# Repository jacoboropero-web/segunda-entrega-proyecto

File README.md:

# Estación de Monitoreo Ambiental con Ventilación Automática (ESP32)

Proyecto del curso Diseño Electrónico CAD, Universidad Autónoma de Manizales.
Autores: Jacobo Ropero y Santiago Rueda. Docente: Iván Alberto Arias.

## Contenido

| Carpeta | Contenido |
|---|---|
| `reporte/` | Reporte de Avance 2 (formato IEEE, PDF) |
| `hardware/estacion_kicad/` | Proyecto KiCad 7: esquemático jerárquico (3 hojas), PCB de 4 capas de 80 × 60 mm y librería de símbolos propia |
| `hardware/estacion_kicad/fab/` | Archivos de fabricación: Gerber y taladrado, BOM y CPL para JLCPCB, esquemático en PDF |
| `firmware/` | Firmware preliminar para ESP32-WROOM-32E (PlatformIO/Arduino), con 15 pruebas unitarias de la lógica de control. Ver `firmware/README.md` |
| `imagenes/` | Capturas de KiCad: editor de esquemas, ERC, editor de placas, pistas, ratsnest y vistas 3D |

## Abrir el proyecto

Abrir `hardware/estacion_kicad/estacion.kicad_pro` con KiCad 7 o posterior.

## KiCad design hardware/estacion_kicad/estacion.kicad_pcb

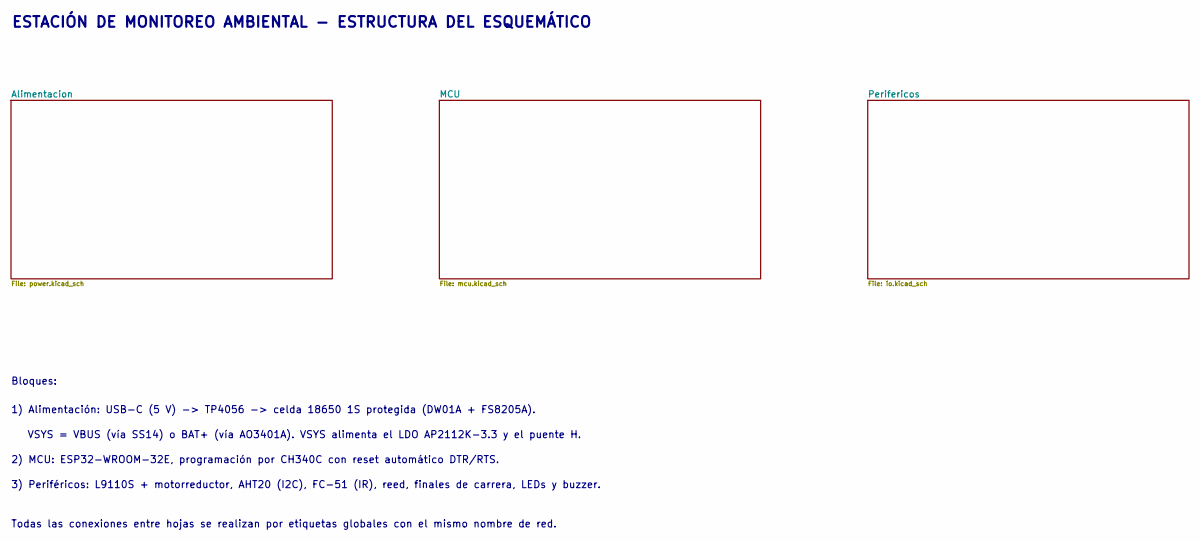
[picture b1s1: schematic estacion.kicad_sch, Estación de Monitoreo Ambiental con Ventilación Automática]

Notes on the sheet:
ESTACIÓN DE MONITOREO AMBIENTAL - ESTRUCTURA DEL ESQUEMÁTICO
Bloques:
1) Alimentación: USB-C (5 V) -> TP4056 -> celda 18650 1S protegida (DW01A + FS8205A).
VSYS = VBUS (vía SS14) o BAT+ (vía AO3401A). VSYS alimenta el LDO AP2112K-3.3 y el puente H.
2) MCU: ESP32-WROOM-32E, programación por CH340C con reset automático DTR/RTS.
3) Periféricos: L9110S + motorreductor, AHT20 (I2C), FC-51 (IR), reed, finales de carrera, LEDs y buzzer.
Todas las conexiones entre hojas se realizan por etiquetas globales con el mismo nombre de red.

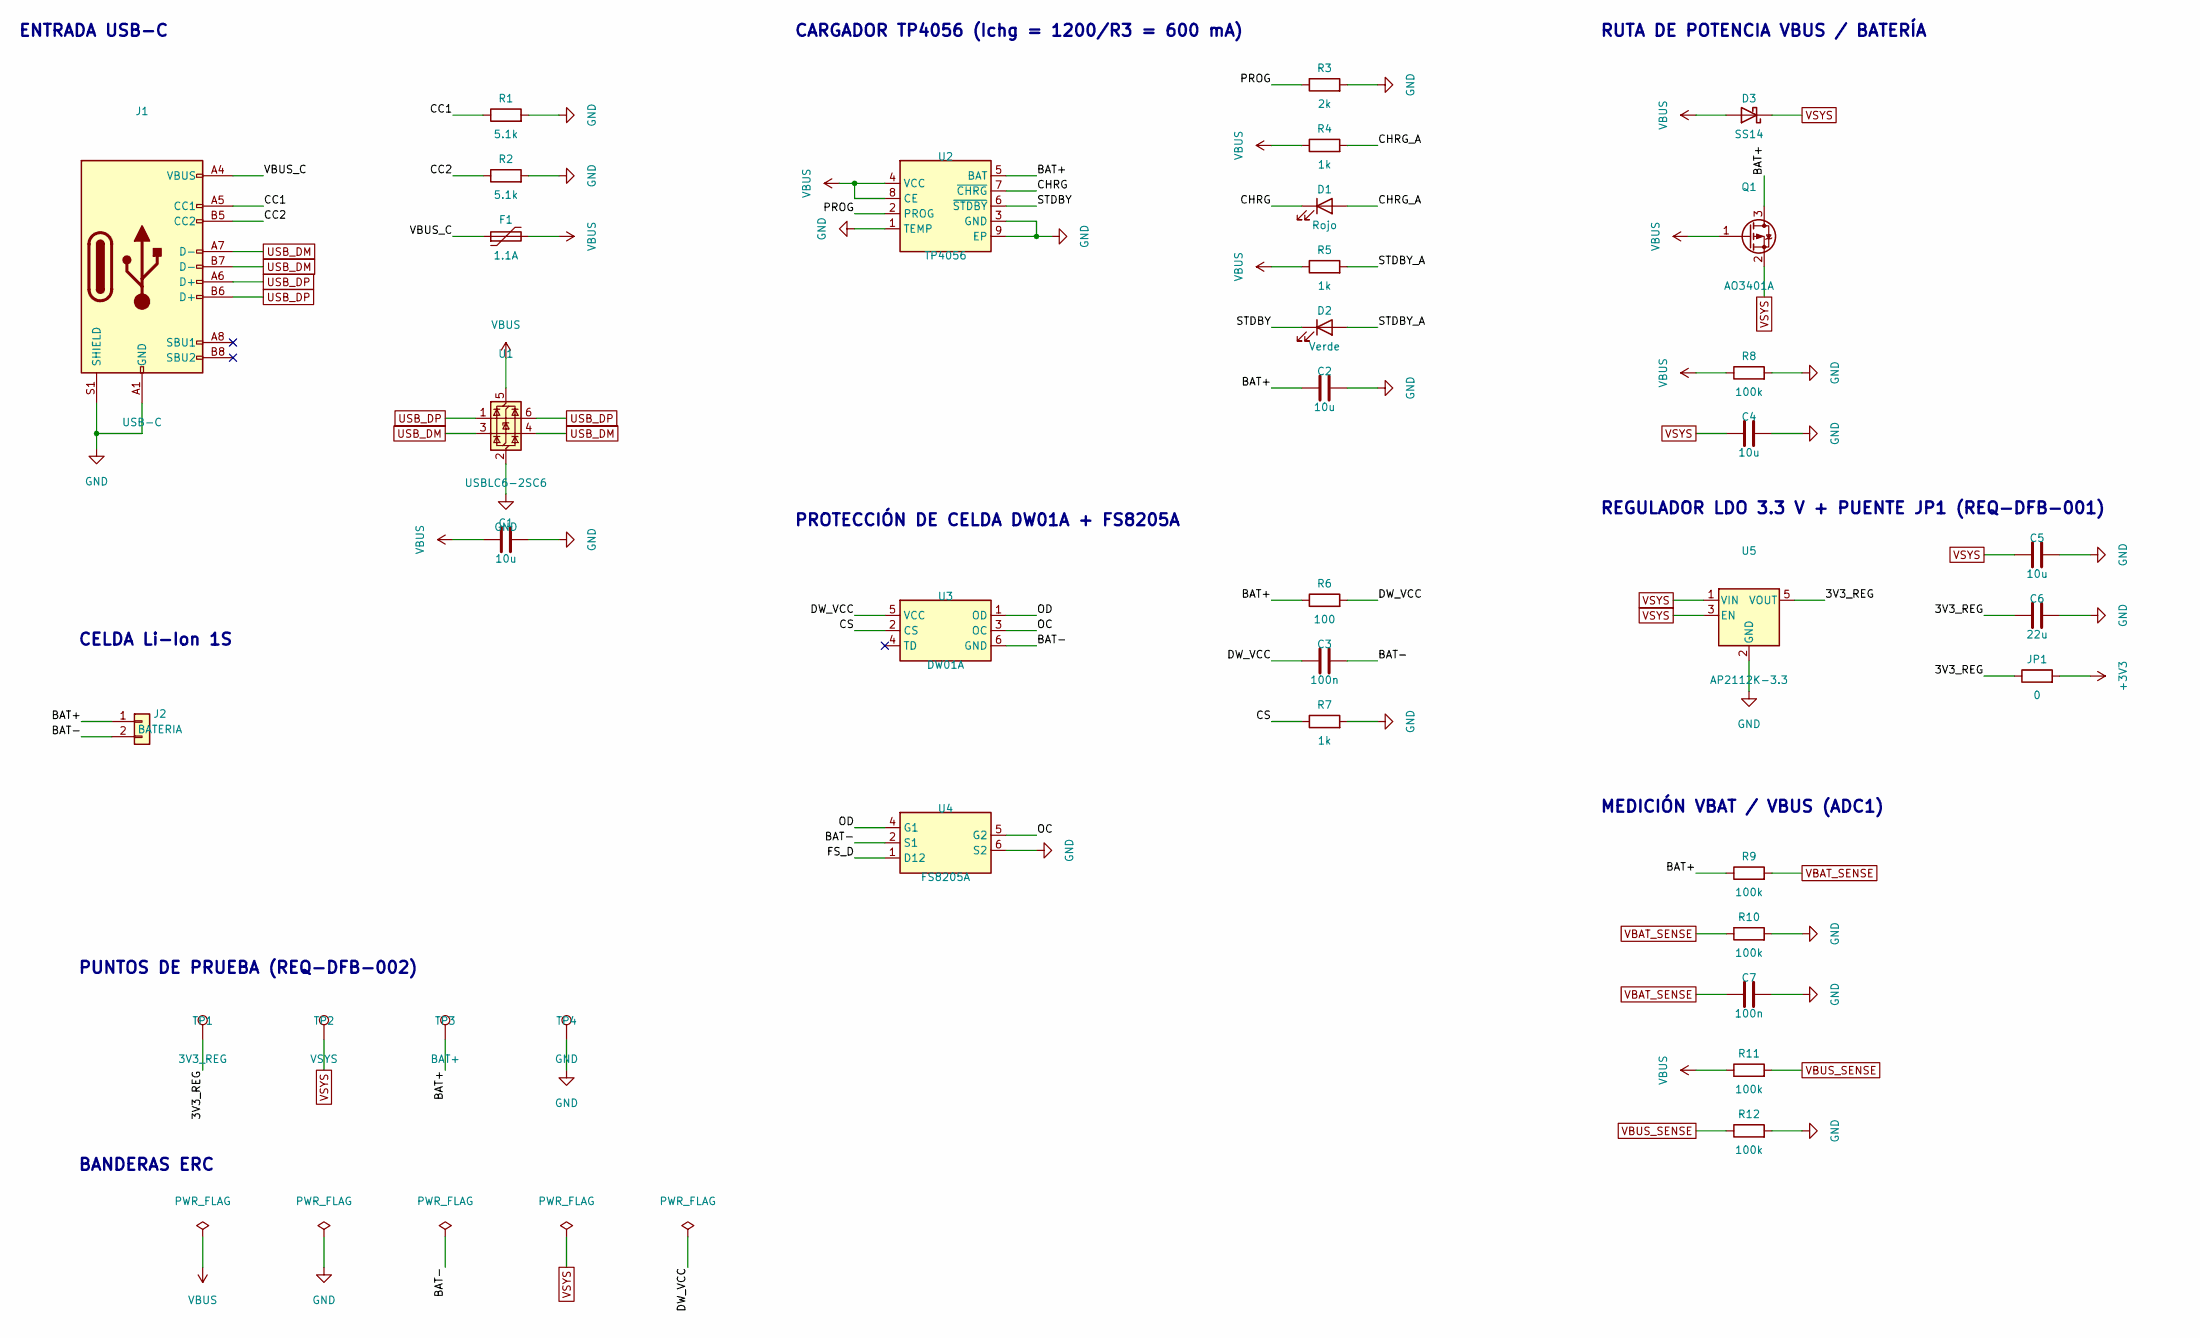
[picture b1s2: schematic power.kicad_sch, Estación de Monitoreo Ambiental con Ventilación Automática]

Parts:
C1, C2, C4, C5: 10u; C_0805_2012Metric; MPN 10uF 16V X5R 0805
C3, C7: 100n; C_0603_1608Metric; MPN 100n
C6: 22u; C_0805_2012Metric; MPN 22uF 10V X5R 0805
D1: Rojo; LED_0603_1608Metric; MPN LED 0603 Rojo
D2: Verde; LED_0603_1608Metric; MPN LED 0603 Verde
D3: SS14; D_SMA; MPN SS14 40V 1A Schottky
F1: 1.1A; Fuse_1206_3216Metric; MPN 1206L110 (PTC 1.1 A)
J1: USB-C; USB_C_Receptacle_HRO_TYPE-C-31-M-12; MPN HRO TYPE-C-31-M-12
J2: BATERIA; JST_PH_B2B-PH-K_1x02_P2.00mm_Vertical; MPN JST PH 2P (celda 18650 1S)
JP1: 0; R_0805_2012Metric; MPN Puente 0 Ohm 0805 (REQ-DFB-001)
Q1: AO3401A; SOT-23; MPN AO3401A P-MOSFET
R1, R2: 5.1k; R_0603_1608Metric; MPN 0603 5.1k 1%
R3: 2k; R_0603_1608Metric; MPN 0603 2k 1%
R4, R5, R7: 1k; R_0603_1608Metric; MPN 0603 1k 1%
R6: 100; R_0603_1608Metric; MPN 0603 100 1%
R8, R9, R10, R11, R12: 100k; R_0603_1608Metric; MPN 0603 100k 1%
TP1: 3V3_REG; TestPoint_Pad_D1.5mm; MPN Pad prueba 1.5 mm
TP2: VSYS; TestPoint_Pad_D1.5mm; MPN Pad prueba 1.5 mm
TP3: BAT+; TestPoint_Pad_D1.5mm; MPN Pad prueba 1.5 mm
TP4: GND; TestPoint_Pad_D1.5mm; MPN Pad prueba 1.5 mm
U1: USBLC6-2SC6; SOT-23-6; MPN USBLC6-2SC6
U2: TP4056; SOIC-8-1EP_3.9x4.9mm_P1.27mm_EP2.29x3mm; MPN TP4056 (ESOP-8)
U3: DW01A; SOT-23-6; MPN DW01A
U4: FS8205A; TSSOP-8_4.4x3mm_P0.65mm; MPN FS8205A
U5: AP2112K-3.3; SOT-23-5; MPN AP2112K-3.3TRG1

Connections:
3V3_REG: C6.1, JP1.1, TP1.1, U5.5 (VOUT)
+3V3: JP1.2; also elsewhere on the board
BAT+: C2.1, J2.1, Q1.3 (D), R6.1, R9.1, TP3.1, U2.5 (BAT)
BAT-: C3.2, J2.2, U3.6 (GND), U4.2 (S1), U4.3 (S1)
CC1: J1.A5 (CC1), R1.1
CC2: J1.B5 (CC2), R2.1
CHRG: D1.1 (K), U2.7 (~CHRG)
CHRG_A: D1.2 (A), R4.2
CS: R7.1, U3.2 (CS)
DW_VCC: C3.1, R6.2, U3.5 (VCC)
FS_D: U4.1 (D12), U4.8 (D12)
GND: C1.2, C2.2, C4.2, C5.2, C6.2, C7.2, J1.A1 (GND), J1.A12 (GND), J1.B1 (GND), J1.B12 (GND), J1.S1 (SHIELD), R1.2, R2.2, R3.2, R7.2, R8.2, R10.2, R12.2, TP4.1, U1.2 (GND), U2.1 (TEMP), U2.3 (GND), U2.9 (EP), U4.6 (S2), U4.7 (S2), U5.2 (GND); also elsewhere on the board
OC: U3.3 (OC), U4.5 (G2)
OD: U3.1 (OD), U4.4 (G1)
PROG: R3.1, U2.2 (PROG)
STDBY: D2.1 (K), U2.6 (~STDBY)
STDBY_A: D2.2 (A), R5.2
USB_DM: J1.A7 (D-), J1.B7 (D-), U1.3 (I/O2), U1.4 (I/O2); also elsewhere on the board
USB_DP: J1.A6 (D+), J1.B6 (D+), U1.1 (I/O1), U1.6 (I/O1); also elsewhere on the board
VBAT_SENSE: C7.1, R9.2, R10.1; also elsewhere on the board
VBUS: C1.1, D3.2 (A), F1.2, Q1.1 (G), R4.1, R5.1, R8.1, R11.1, U1.5 (VBUS), U2.4 (VCC), U2.8 (CE)
VBUS_C: F1.1, J1.A4 (VBUS), J1.A9 (VBUS), J1.B4 (VBUS), J1.B9 (VBUS)
VBUS_SENSE: R11.2, R12.1; also elsewhere on the board
VSYS: C4.1, C5.1, D3.1 (K), Q1.2 (S), TP2.1, U5.1 (VIN), U5.3 (EN); also elsewhere on the board

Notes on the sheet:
ENTRADA USB-C
CARGADOR TP4056 (Ichg = 1200/R3 = 600 mA)
PROTECCIÓN DE CELDA DW01A + FS8205A
RUTA DE POTENCIA VBUS / BATERÍA
REGULADOR LDO 3.3 V + PUENTE JP1 (REQ-DFB-001)
MEDICIÓN VBAT / VBUS (ADC1)
CELDA Li-Ion 1S
PUNTOS DE PRUEBA (REQ-DFB-002)
BANDERAS ERC

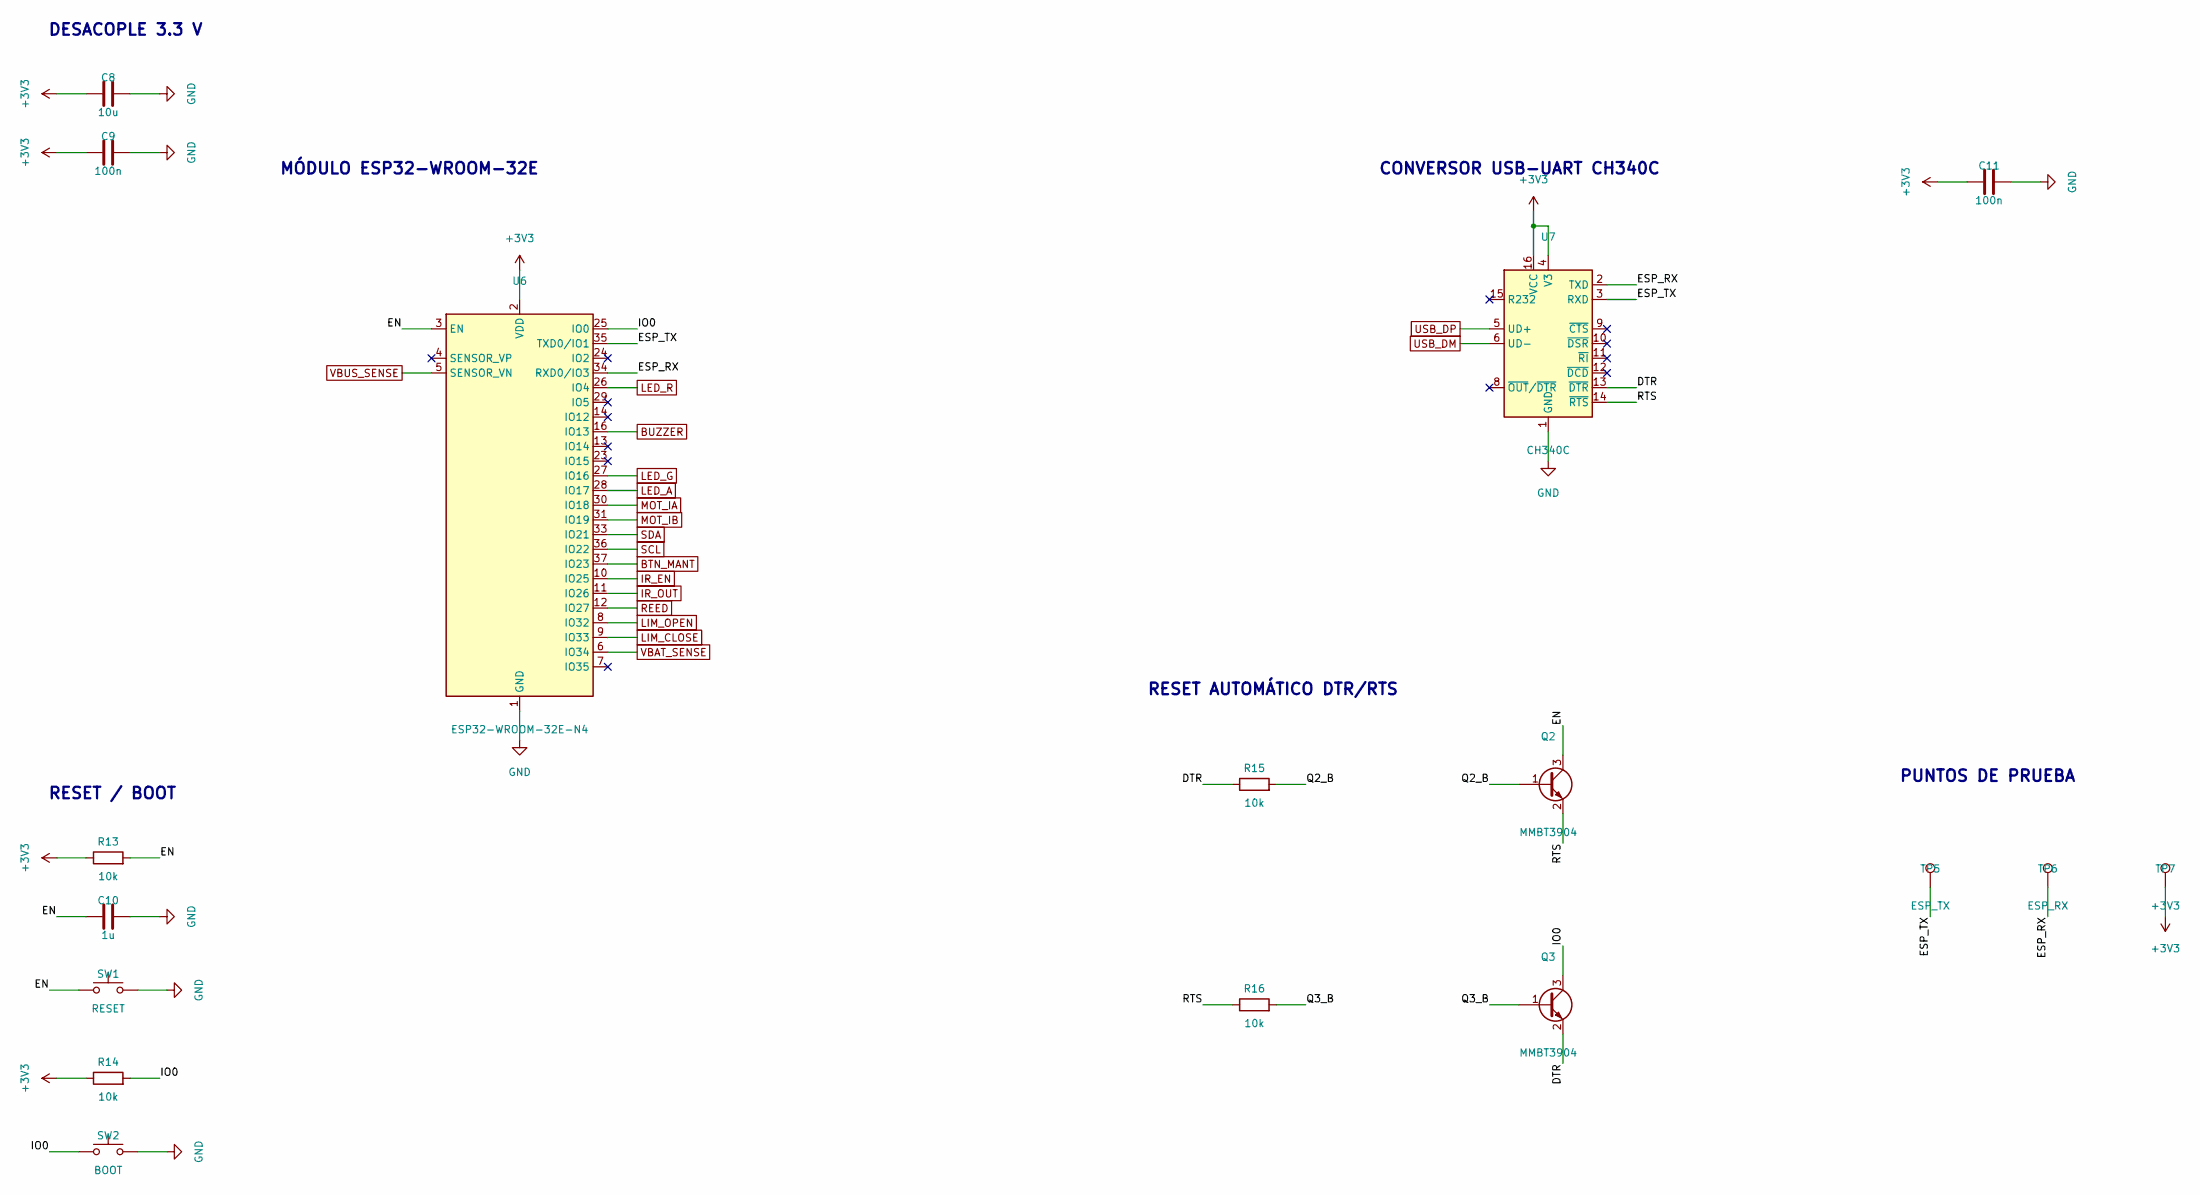
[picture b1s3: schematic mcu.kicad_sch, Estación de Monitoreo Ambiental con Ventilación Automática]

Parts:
C8: 10u; C_0805_2012Metric; MPN 10uF 16V X5R 0805
C9, C11: 100n; C_0603_1608Metric; MPN 100n
C10: 1u; C_0603_1608Metric; MPN 1u
Q2, Q3: MMBT3904; SOT-23; MPN MMBT3904
R13, R14, R15, R16: 10k; R_0603_1608Metric; MPN 0603 10k 1%
SW1: RESET; SW_Push_1P1T_XKB_TS-1187A; MPN TS-1187A
SW2: BOOT; SW_Push_1P1T_XKB_TS-1187A; MPN TS-1187A
TP5: ESP_TX; TestPoint_Pad_D1.5mm; MPN Pad prueba 1.5 mm
TP6: ESP_RX; TestPoint_Pad_D1.5mm; MPN Pad prueba 1.5 mm
TP7: +3V3; TestPoint_Pad_D1.5mm; MPN Pad prueba 1.5 mm
U6: ESP32-WROOM-32E-N4; ESP32-WROOM-32D; MPN ESP32-WROOM-32E-N4
U7: CH340C; SOIC-16_3.9x9.9mm_P1.27mm; MPN CH340C

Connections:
+3V3: C8.1, C9.1, C11.1, R13.1, R14.1, TP7.1, U6.2 (VDD), U7.4 (V3), U7.16 (VCC); also elsewhere on the board
BTN_MANT: U6.37 (IO23); also elsewhere on the board
BUZZER: U6.16 (IO13); also elsewhere on the board
DTR: Q3.2 (E), R15.1, U7.13 (~DTR)
EN: C10.1, Q2.3 (C), R13.2, SW1.1, U6.3 (EN)
ESP_RX: TP6.1, U6.34 (RXD0/IO3), U7.2 (TXD)
ESP_TX: TP5.1, U6.35 (TXD0/IO1), U7.3 (RXD)
GND: C8.2, C9.2, C10.2, C11.2, SW1.2, SW2.2, U6.1 (GND), U6.15 (GND), U6.38 (GND), U6.39 (GND), U7.1 (GND); also elsewhere on the board
IO0: Q3.3 (C), R14.2, SW2.1, U6.25 (IO0)
IR_EN: U6.10 (IO25); also elsewhere on the board
IR_OUT: U6.11 (IO26); also elsewhere on the board
LED_A: U6.28 (IO17); also elsewhere on the board
LED_G: U6.27 (IO16); also elsewhere on the board
LED_R: U6.26 (IO4); also elsewhere on the board
LIM_CLOSE: U6.9 (IO33); also elsewhere on the board
LIM_OPEN: U6.8 (IO32); also elsewhere on the board
MOT_IA: U6.30 (IO18); also elsewhere on the board
MOT_IB: U6.31 (IO19); also elsewhere on the board
Q2_B: Q2.1 (B), R15.2
Q3_B: Q3.1 (B), R16.2
REED: U6.12 (IO27); also elsewhere on the board
RTS: Q2.2 (E), R16.1, U7.14 (~RTS)
SCL: U6.36 (IO22); also elsewhere on the board
SDA: U6.33 (IO21); also elsewhere on the board
USB_DM: U7.6 (UD-); also elsewhere on the board
USB_DP: U7.5 (UD+); also elsewhere on the board
VBAT_SENSE: U6.6 (IO34); also elsewhere on the board
VBUS_SENSE: U6.5 (SENSOR_VN); also elsewhere on the board

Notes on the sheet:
DESACOPLE 3.3 V
MÓDULO ESP32-WROOM-32E
RESET / BOOT
CONVERSOR USB-UART CH340C
RESET AUTOMÁTICO DTR/RTS
PUNTOS DE PRUEBA

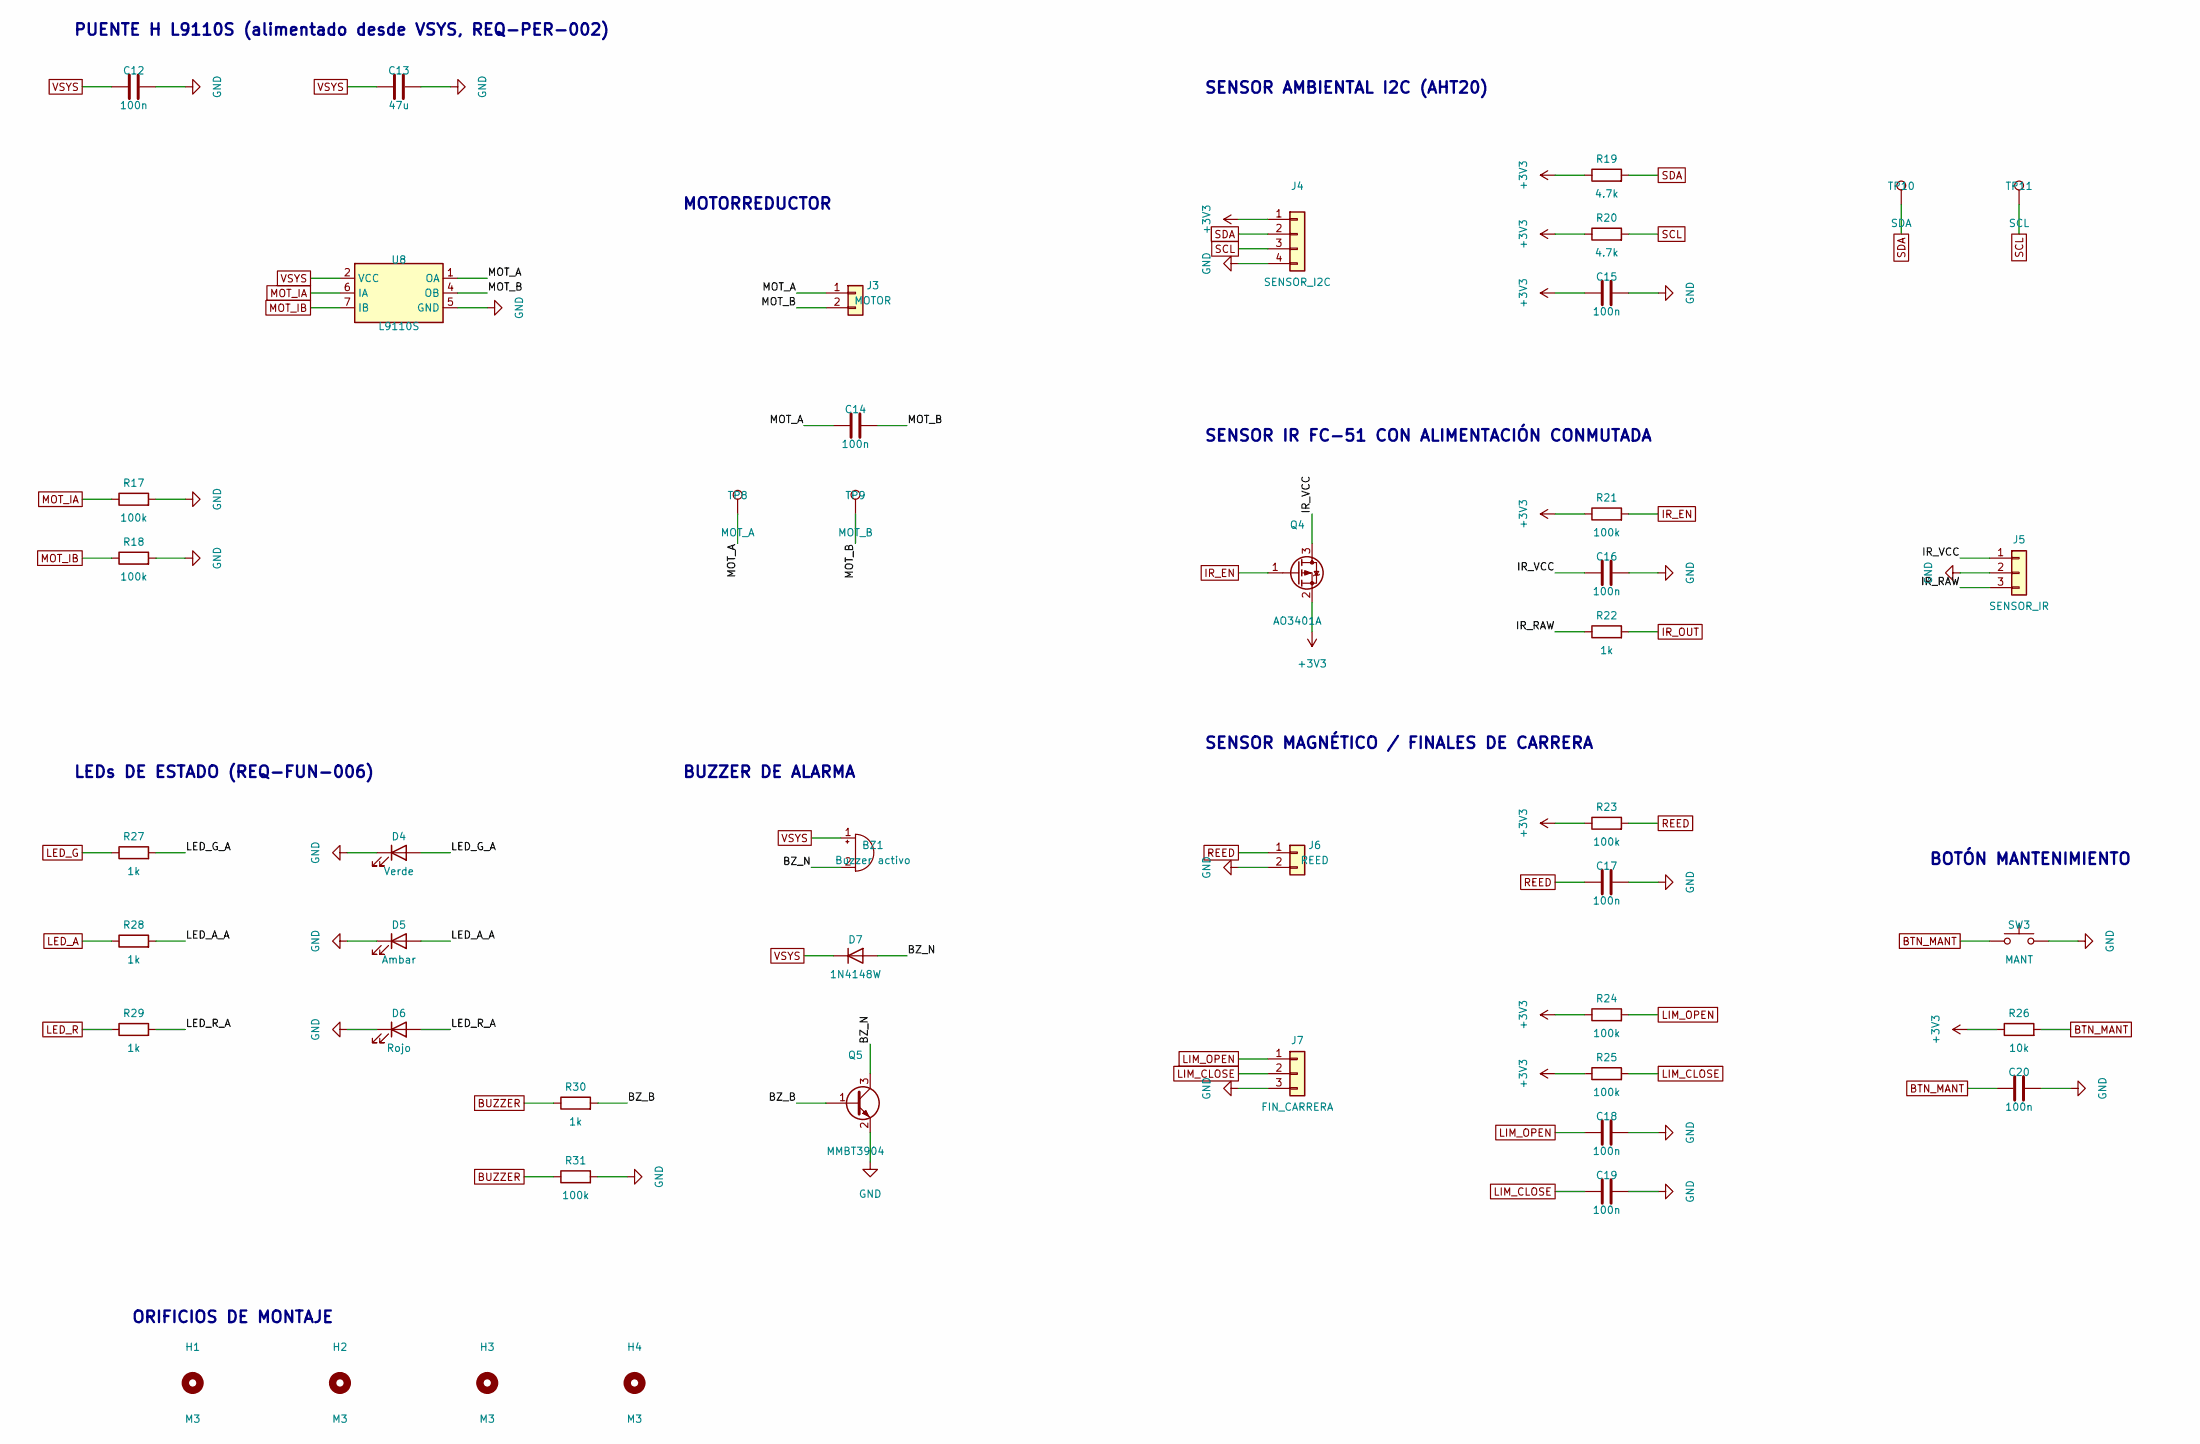
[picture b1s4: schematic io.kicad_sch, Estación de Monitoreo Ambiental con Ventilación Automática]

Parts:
BZ1: Buzzer activo; Buzzer_12x9.5RM7.6; MPN Buzzer activo 12 mm 3-5 V
C12, C14, C15, C16, C17, C18, C19, C20: 100n; C_0603_1608Metric; MPN 100n
C13: 47u; C_1206_3216Metric; MPN 47uF 10V X5R 1206
D4: Verde; LED_0603_1608Metric; MPN LED 0603 Verde
D5: Ambar; LED_0603_1608Metric; MPN LED 0603 Ambar
D6: Rojo; LED_0603_1608Metric; MPN LED 0603 Rojo
D7: 1N4148W; D_SOD-123; MPN 1N4148W
H1, H2, H3, H4: M3; MountingHole_3.2mm_M3; MPN Orificio M3
J3: MOTOR; JST_PH_B2B-PH-K_1x02_P2.00mm_Vertical; MPN JST PH 2P
J4: SENSOR_I2C; JST_PH_B4B-PH-K_1x04_P2.00mm_Vertical; MPN JST PH 4P (módulo AHT20)
J5: SENSOR_IR; JST_PH_B3B-PH-K_1x03_P2.00mm_Vertical; MPN JST PH 3P (módulo FC-51)
J6: REED; JST_PH_B2B-PH-K_1x02_P2.00mm_Vertical; MPN JST PH 2P
J7: FIN_CARRERA; JST_PH_B3B-PH-K_1x03_P2.00mm_Vertical; MPN JST PH 3P
Q4: AO3401A; SOT-23; MPN AO3401A P-MOSFET
Q5: MMBT3904; SOT-23; MPN MMBT3904
R17, R18, R21, R23, R24, R25, R31: 100k; R_0603_1608Metric; MPN 0603 100k 1%
R19, R20: 4.7k; R_0603_1608Metric; MPN 0603 4.7k 1%
R22, R27, R28, R29, R30: 1k; R_0603_1608Metric; MPN 0603 1k 1%
R26: 10k; R_0603_1608Metric; MPN 0603 10k 1%
SW3: MANT; SW_Push_1P1T_XKB_TS-1187A; MPN TS-1187A
TP8: MOT_A; TestPoint_Pad_D1.5mm; MPN Pad prueba 1.5 mm
TP9: MOT_B; TestPoint_Pad_D1.5mm; MPN Pad prueba 1.5 mm
TP10: SDA; TestPoint_Pad_D1.5mm; MPN Pad prueba 1.5 mm
TP11: SCL; TestPoint_Pad_D1.5mm; MPN Pad prueba 1.5 mm
U8: L9110S; SOIC-8_3.9x4.9mm_P1.27mm; MPN L9110S (SOP-8)

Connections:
+3V3: C15.1, J4.1, Q4.2 (S), R19.1, R20.1, R21.1, R23.1, R24.1, R25.1, R26.1; also elsewhere on the board
BTN_MANT: C20.1, R26.2, SW3.1; also elsewhere on the board
BUZZER: R30.1, R31.1; also elsewhere on the board
BZ_B: Q5.1 (B), R30.2
BZ_N: BZ1.2 (-), D7.2 (A), Q5.3 (C)
GND: C12.2, C13.2, C15.2, C16.2, C17.2, C18.2, C19.2, C20.2, D4.1 (K), D5.1 (K), D6.1 (K), J4.4, J5.2, J6.2, J7.3, Q5.2 (E), R17.2, R18.2, R31.2, SW3.2, U8.5 (GND), U8.8 (GND); also elsewhere on the board
IR_EN: Q4.1 (G), R21.2; also elsewhere on the board
IR_OUT: R22.2; also elsewhere on the board
IR_RAW: J5.3, R22.1
IR_VCC: C16.1, J5.1, Q4.3 (D)
LED_A: R28.1; also elsewhere on the board
LED_A_A: D5.2 (A), R28.2
LED_G: R27.1; also elsewhere on the board
LED_G_A: D4.2 (A), R27.2
LED_R: R29.1; also elsewhere on the board
LED_R_A: D6.2 (A), R29.2
LIM_CLOSE: C19.1, J7.2, R25.2; also elsewhere on the board
LIM_OPEN: C18.1, J7.1, R24.2; also elsewhere on the board
MOT_A: C14.1, J3.1, TP8.1, U8.1 (OA)
MOT_B: C14.2, J3.2, TP9.1, U8.4 (OB)
MOT_IA: R17.1, U8.6 (IA); also elsewhere on the board
MOT_IB: R18.1, U8.7 (IB); also elsewhere on the board
REED: C17.1, J6.1, R23.2; also elsewhere on the board
SCL: J4.3, R20.2, TP11.1; also elsewhere on the board
SDA: J4.2, R19.2, TP10.1; also elsewhere on the board
VSYS: BZ1.1 (+), C12.1, C13.1, D7.1 (K), U8.2 (VCC), U8.3 (VCC); also elsewhere on the board

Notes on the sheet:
PUENTE H L9110S (alimentado desde VSYS, REQ-PER-002)
MOTORREDUCTOR
SENSOR AMBIENTAL I2C (AHT20)
SENSOR IR FC-51 CON ALIMENTACIÓN CONMUTADA
SENSOR MAGNÉTICO / FINALES DE CARRERA
BOTÓN MANTENIMIENTO
LEDs DE ESTADO (REQ-FUN-006)
BUZZER DE ALARMA
ORIFICIOS DE MONTAJE

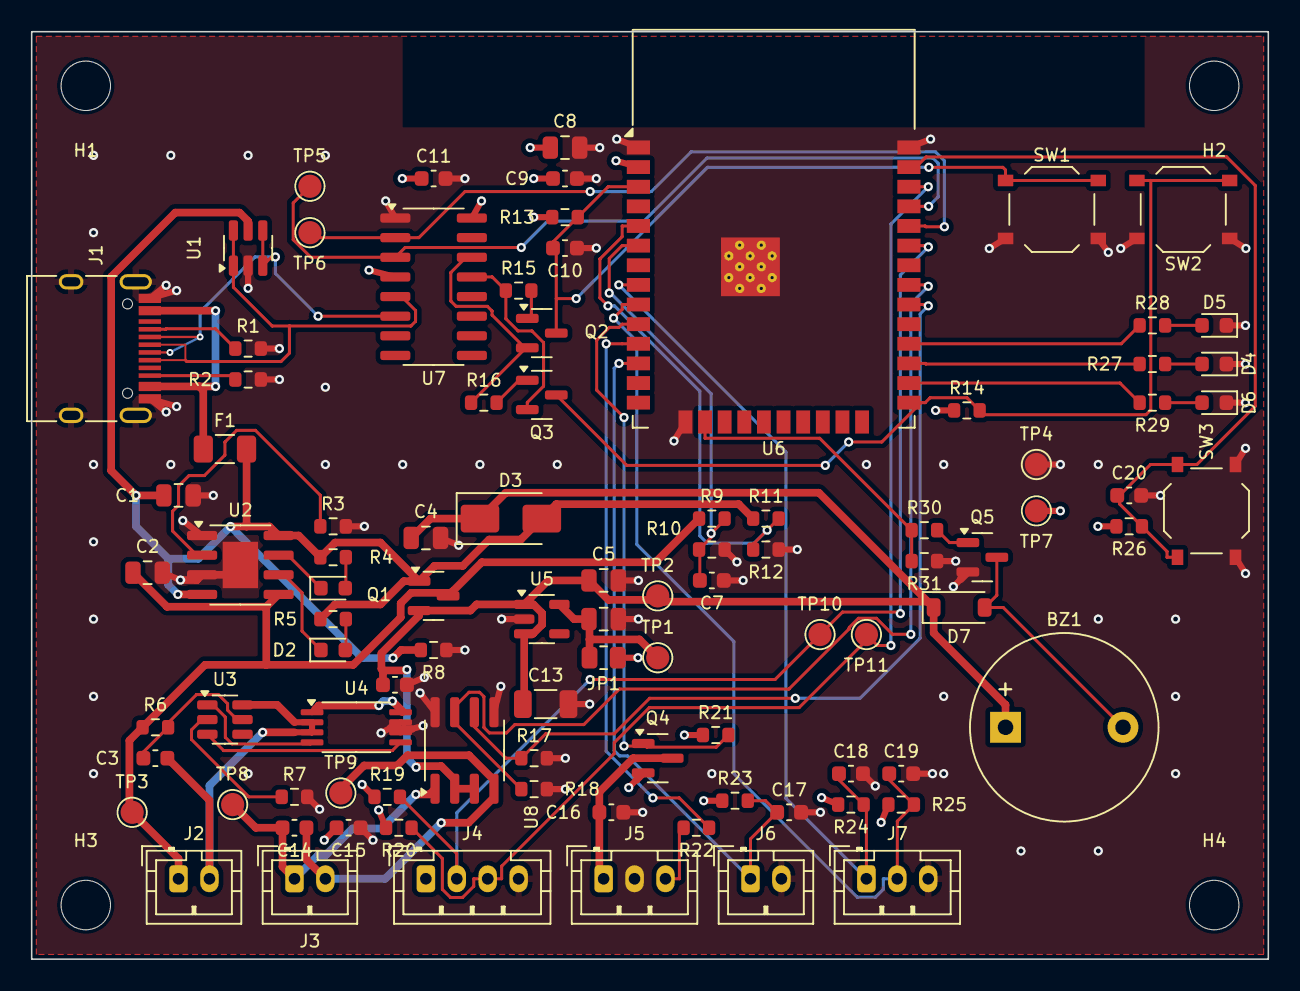
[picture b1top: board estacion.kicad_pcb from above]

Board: 4 copper layers, 80.0 x 60.0 mm, 99 parts (0 on the bottom side), 55 nets.

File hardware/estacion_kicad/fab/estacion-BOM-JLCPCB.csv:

Comment,Designator,Footprint,LCSC Part #
USB-C,J1,USB_C_Receptacle_HRO_TYPE-C-31-M-12,C165948
5.1k,"R1,R2",R_0603_1608Metric,
1.1A,F1,Fuse_1206_3216Metric,
USBLC6-2SC6,U1,SOT-23-6,C7519
10u,"C1,C2,C4,C5,C8",C_0805_2012Metric,
TP4056,U2,SOIC-8-1EP_3.9x4.9mm_P1.27mm_EP2.29x3mm,C16581
2k,R3,R_0603_1608Metric,
1k,"R4,R5,R7,R22,R27,R28,R29,R30",R_0603_1608Metric,
Rojo,"D1,D6",LED_0603_1608Metric,
Verde,"D2,D4",LED_0603_1608Metric,
DW01A,U3,SOT-23-6,C351410
FS8205A,U4,TSSOP-8_4.4x3mm_P0.65mm,C16052
100,R6,R_0603_1608Metric,
100n,"C3,C7,C9,C11,C12,C14,C15,C16,C17,C18,C19,C20",C_0603_1608Metric,
SS14,D3,D_SMA,C2480
AO3401A,"Q1,Q4",SOT-23,C15127
100k,"R8,R9,R10,R11,R12,R17,R18,R21,R23,R24,R25,R31",R_0603_1608Metric,
AP2112K-3.3,U5,SOT-23-5,C51118
22u,C6,C_0805_2012Metric,
0,JP1,R_0805_2012Metric,
ESP32-WROOM-32E-N4,U6,ESP32-WROOM-32D,C701341
10k,"R13,R14,R15,R16,R26",R_0603_1608Metric,
1u,C10,C_0603_1608Metric,
RESET,SW1,SW_Push_1P1T_XKB_TS-1187A,C318884
BOOT,SW2,SW_Push_1P1T_XKB_TS-1187A,C318884
CH340C,U7,SOIC-16_3.9x9.9mm_P1.27mm,C84681
MMBT3904,"Q2,Q3,Q5",SOT-23,C20526
L9110S,U8,SOIC-8_3.9x4.9mm_P1.27mm,C85174
47u,C13,C_1206_3216Metric,
4.7k,"R19,R20",R_0603_1608Metric,
MANT,SW3,SW_Push_1P1T_XKB_TS-1187A,C318884
Ambar,D5,LED_0603_1608Metric,
1N4148W,D7,D_SOD-123,C81598

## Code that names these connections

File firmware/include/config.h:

// Estación de Monitoreo Ambiental con Ventilación Automática - Firmware v0.2
// Asignación de pines (ESP32-WROOM-32E) según esquemático v2.0 y parámetros de operación.
#pragma once
#include <stdint.h>

// ---------------- Pines ----------------
#define PIN_SDA         21   // Bus I2C sensor AHT20 (J4)
#define PIN_SCL         22
#define PIN_IR_OUT      26   // Salida del módulo FC-51 (activa en bajo), vía R22
#define PIN_IR_EN       25   // Habilita alimentación del FC-51 (Q4, activo en bajo)
#define PIN_BTN_MANT    23   // Botón SW3 modo mantenimiento (activo en bajo)
#define PIN_REED        27   // Sensor magnético: LOW = puerta cerrada, HIGH = abierta
#define PIN_LIM_OPEN    32   // Final de carrera "rejilla abierta" (activo en bajo, opcional)
#define PIN_LIM_CLOSE   33   // Final de carrera "rejilla cerrada" (activo en bajo, opcional)
#define PIN_BUZZER      13   // Buzzer activo vía Q5
#define PIN_LED_R        4
#define PIN_LED_G       16
#define PIN_LED_A       17
#define PIN_MOT_IA      18   // L9110S IA (PWM)
#define PIN_MOT_IB      19   // L9110S IB (PWM)
#define PIN_VBAT        34   // Divisor 100k/100k desde BAT+ (ADC1_CH6)
#define PIN_VBUS        39   // Divisor 100k/100k desde VBUS (ADC1_CH3)

// ---------------- Temporización (REQ-FUN-001..005) ----------------
#define T_MUESTREO_MS        5000UL   // REQ-FUN-001: lectura cada 5 s
#define T_CIERRE_SEGURO_MS  30000UL   // REQ-FUN-003: 30 s en rango seguro antes de cerrar
#define T_ALARMA_MS          5000UL   // REQ-FUN-004: buzzer 5 s
#define T_OVERRIDE_MS       60000UL   // REQ-FUN-005: control manual 60 s
#define T_MOTOR_MAX_MS       1500UL   // tiempo máximo de recorrido (REQ-FUN-002: < 2 s)
#define T_MANT_MAX_MS      900000UL   // el modo mantenimiento se desactiva solo a los 15 min
#define T_IR_POLL_MS          100UL   // muestreo del sensor IR con alimentación conmutada
#define T_IR_ESTAB_US        3000UL   // estabilización del FC-51 tras energizarlo
#define T_PUBLICAR_MS       30000UL   // envío de telemetría por MQTT
#define FALLAS_SENSOR_MAX        3    // lecturas fallidas consecutivas para declarar falla

// ---------------- Umbrales por defecto ----------------
#define T_ABRIR_C          35.0f   // REQ-FUN-002
#define T_CERRAR_C         33.0f   // histéresis de 2 °C
#define RH_ABRIR           80.0f
#define RH_CERRAR          75.0f
#define T_VERDE_MAX        30.0f   // REQ-FUN-006: verde por debajo de 30 °C y 65 %RH
#define RH_VERDE_MAX       65.0f

// ---------------- Batería ----------------
#define VBAT_BAJA_MV        3550   // alerta: por debajo de este valor el LDO puede salir de regulación en ráfagas Wi-Fi
#define VBAT_CRITICA_MV     3400   // apagado preventivo (deep sleep)
#define DIVISOR_VBAT        2.0f

// ---------------- Motor ----------------
#define MOTOR_PWM_FREQ     20000
#define MOTOR_PWM_BITS         8
#define MOTOR_DUTY           204   // 80 %
